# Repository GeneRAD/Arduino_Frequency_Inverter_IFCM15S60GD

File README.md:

# Frequency-Inverter-IFCM15S60GD
A frequency inverter with IFCM15S60GD up to 2kW.

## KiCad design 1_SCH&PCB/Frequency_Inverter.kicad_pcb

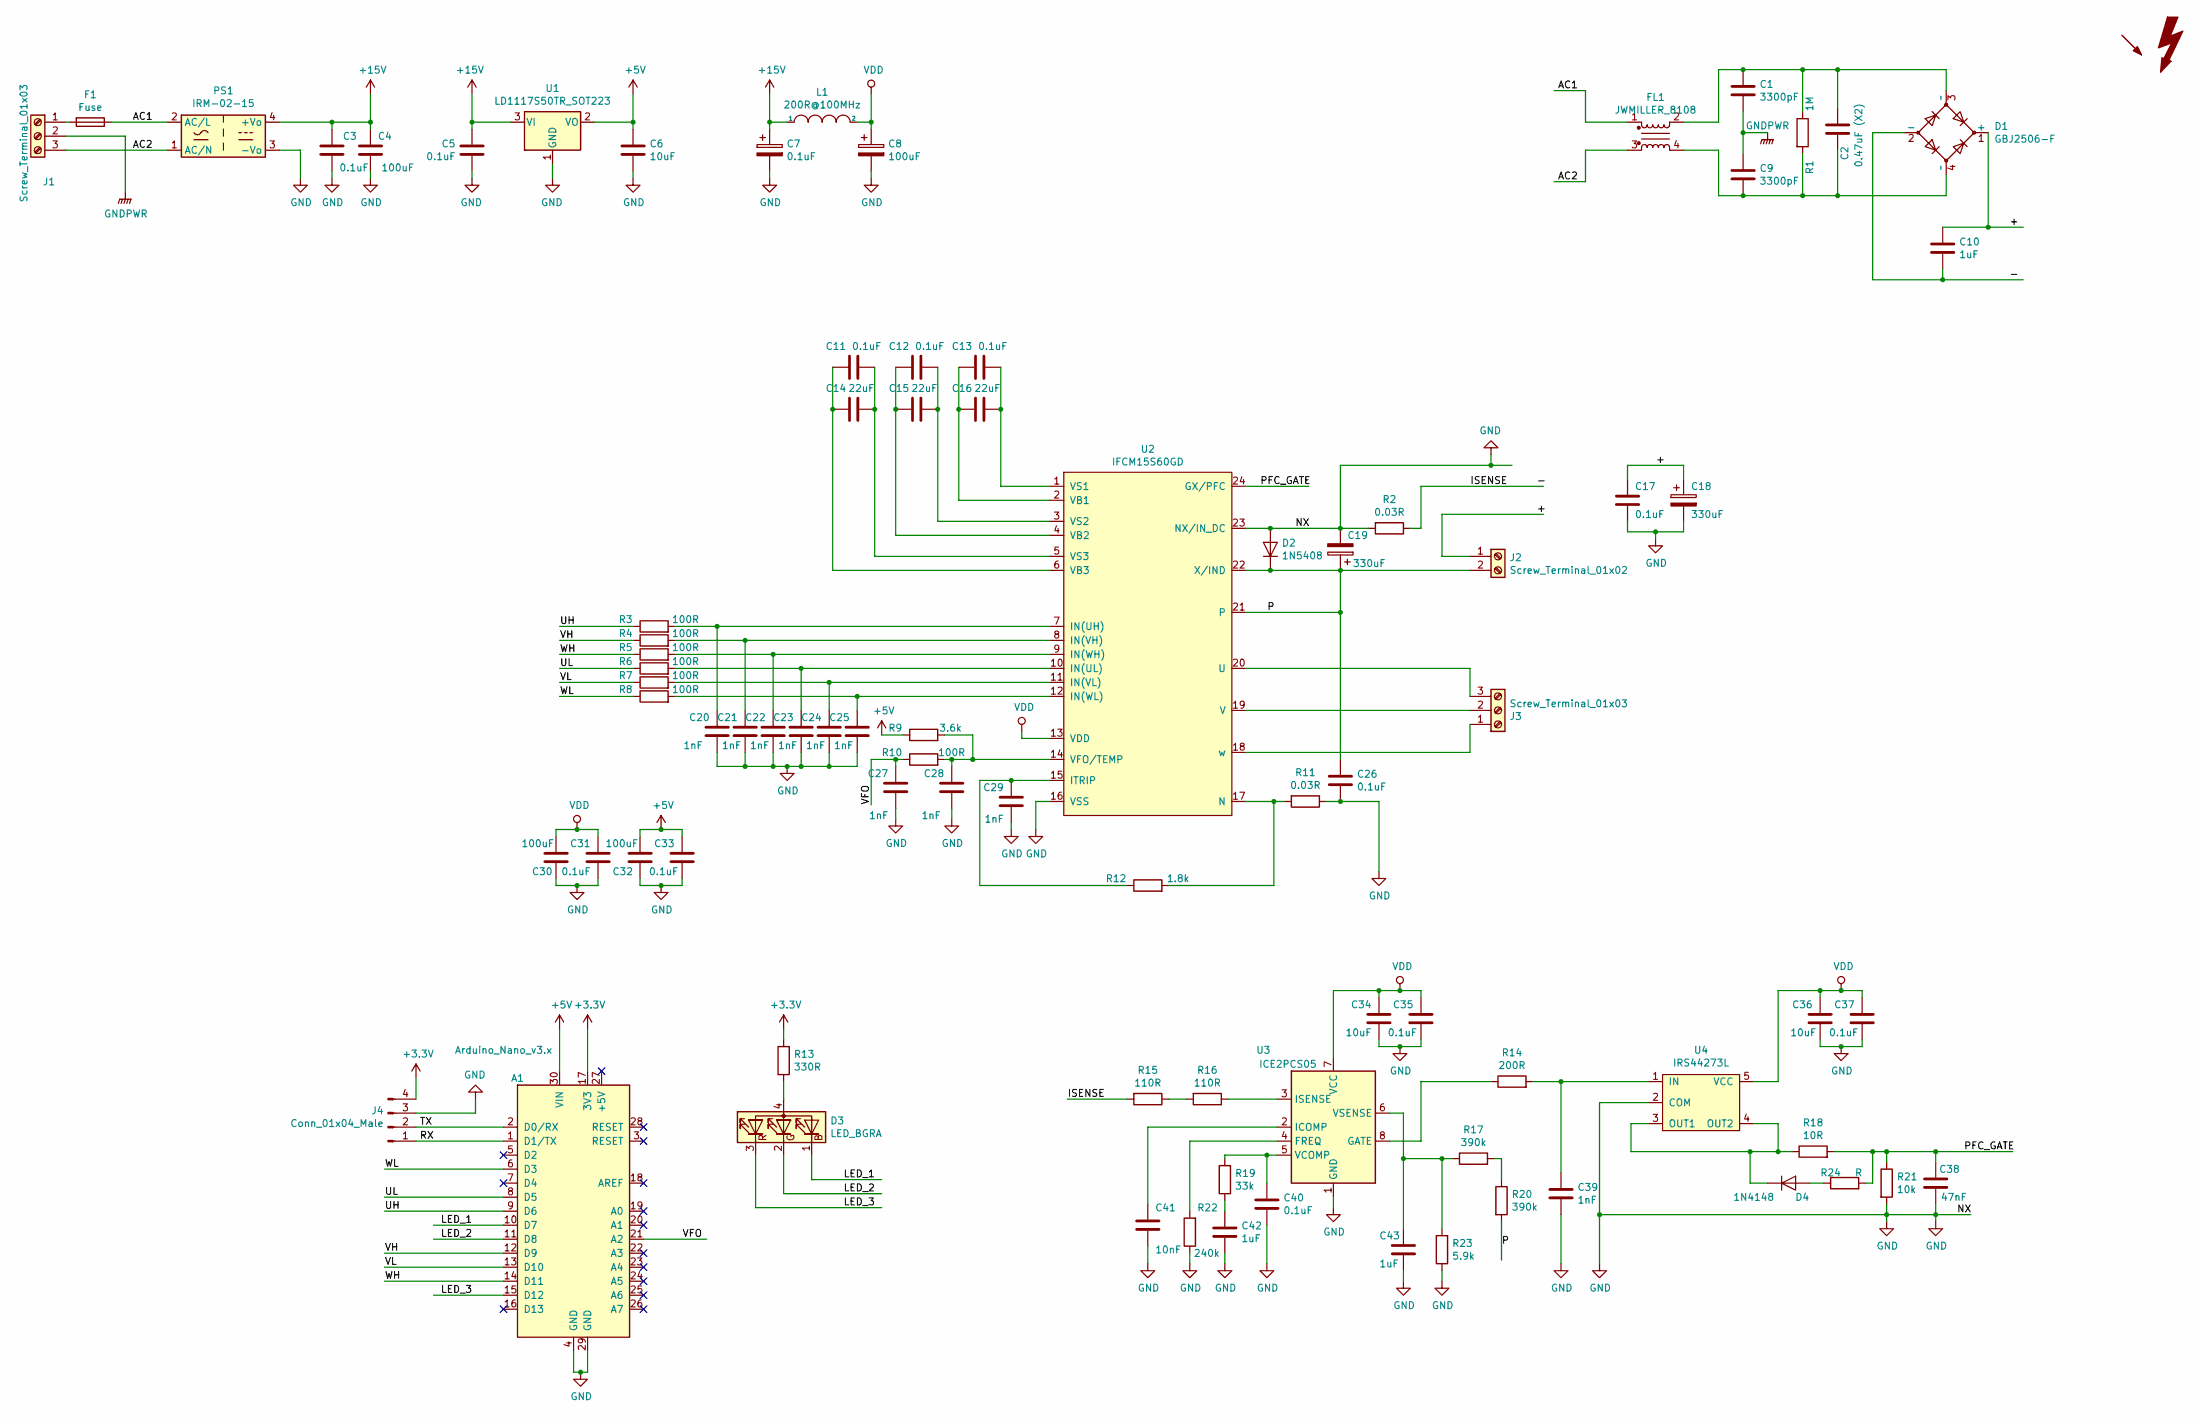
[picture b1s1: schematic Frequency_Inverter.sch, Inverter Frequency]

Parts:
A1: Arduino_Nano_v3.x; Arduino_Nano
C1, C9: 3300pF; C_Disc_D7.5mm_W5.0mm_P7.50mm
C2: 0.47uF (X2); C_Rect_L26.5mm_W7.0mm_P22.50mm_MKS4
C3, C5, C7, C11, C12, C13, C31, C33, C35, C37, C40: 0.1uF; C_0805_2012Metric_Pad1.15x1.40mm_HandSolder
C4, C8, C30, C32: 100uF; CP_Elec_6.3x4.5
C6, C34, C36: 10uF; C_0805_2012Metric_Pad1.15x1.40mm_HandSolder
C10: 1uF; C_1825_4564Metric_Pad1.88x6.70mm_HandSolder
C14, C15, C16: 22uF; C_1206_3216Metric_Pad1.42x1.75mm_HandSolder
C17, C26: 0.1uF; C_1825_4564Metric_Pad1.88x6.70mm_HandSolder
C18, C19: 330uF; CP_Radial_D35.0mm_P10.00mm_SnapIn
C20, C21, C22, C23, C24, C25, C27, C28, C29, C39: 1nF; C_0805_2012Metric_Pad1.15x1.40mm_HandSolder
C38: 47nF; C_0805_2012Metric_Pad1.15x1.40mm_HandSolder
C41: 10nF; C_0805_2012Metric_Pad1.15x1.40mm_HandSolder
C42, C43: 1uF; C_0805_2012Metric_Pad1.15x1.40mm_HandSolder
D1: GBJ2506-F; Diode_Bridge_Vishay_KBL
D2: 1N5408; D_DO-201AD_P15.24mm_Horizontal
D3: LED_BGRA; LED_Cree-PLCC4_5x5mm_CW
D4: 1N4148; D_0805_2012Metric
F1: Fuse; Fuse_Littelfuse-LVR100
FL1: JWMILLER_8108; L_CommonMode_Wuerth_WE-CMB-XS
J1, J3: Screw_Terminal_01x03; TerminalBlock_Altech_AK300-3_P5.00mm
J2: Screw_Terminal_01x02; TerminalBlock_Altech_AK300-2_P5.00mm
J4: Conn_01x04_Male; PinHeader_1x04_P2.54mm_Horizontal
L1: 200R@100MHz; L_0805_2012Metric_Pad1.15x1.40mm_HandSolder
PS1: IRM-02-15; Converter_ACDC_MeanWell_IRM-02-xx_THT
R1: 1M; R_2512_6332Metric_Pad1.52x3.35mm_HandSolder
R2, R11: 0.03R; R_1218_3246Metric_Pad1.22x4.75mm_HandSolder
R3, R4, R5, R6, R7, R8, R10: 100R; R_0805_2012Metric_Pad1.15x1.40mm_HandSolder
R9: 3.6k; R_0805_2012Metric_Pad1.15x1.40mm_HandSolder
R12: 1.8k; R_0805_2012Metric_Pad1.15x1.40mm_HandSolder
R13: 330R; R_0805_2012Metric_Pad1.15x1.40mm_HandSolder
R14: 200R; R_0805_2012Metric_Pad1.15x1.40mm_HandSolder
R15, R16: 110R; R_0805_2012Metric_Pad1.15x1.40mm_HandSolder
R17, R20: 390k; R_0805_2012Metric_Pad1.15x1.40mm_HandSolder
R18: 10R; R_0805_2012Metric_Pad1.15x1.40mm_HandSolder
R19: 33k; R_0805_2012Metric_Pad1.15x1.40mm_HandSolder
R21: 10k; R_0805_2012Metric_Pad1.15x1.40mm_HandSolder
R22: 240k; R_0805_2012Metric_Pad1.15x1.40mm_HandSolder
R23: 5.9k; R_0805_2012Metric_Pad1.15x1.40mm_HandSolder
R24: R; R_0805_2012Metric_Pad1.15x1.40mm_HandSolder
U1: LD1117S50TR_SOT223; SOT-223-3_TabPin2
U2: IFCM15S60GD; IFCM15S60_24_pins
U3: ICE2PCS05; SOIC-8_3.9x4.9mm_P1.27mm
U4: IRS44273L; SOT-23-5_HandSoldering

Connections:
+3V3: A1.17 (3V3), J4.4, R13.2
+5V: A1.30 (VIN), C6.1, C32.1, C33.2, R9.1, U1.2 (VO)
+15V: C3.1, C4.1, C5.1, C7.1, L1.1, PS1.4 (+Vo), U1.3 (VI)
/+: C10.1, C17.1, C18.1, D1.1 (+), J2.1
/-: C10.2, D1.2 (-), R2.1, R15.2
/AC1: F1.1, FL1.1, PS1.2 (AC/L)
/AC2: FL1.3, J1.3, PS1.1 (AC/N)
/LED_1: A1.10 (D7), D3.1 (BK)
/LED_2: A1.11 (D8), D3.2 (GK)
/LED_3: A1.15 (D12), D3.3 (RK)
/P: C19.1, C26.1, D2.1 (K), J2.2, R20.2, U2.21, U2.22 (X/IND)
/PFC_GATE: C38.2, R18.2, R21.1, R24.2, U2.24 (GX/PFC)
/RX: A1.1 (D1/TX), J4.1
/TX: A1.2 (D0/RX), J4.2
/UH: A1.9 (D6), R3.1
/UL: A1.8 (D5), R6.1
/VFO: A1.21 (A2), C27.2, R10.1
/VH: A1.12 (D9), R4.1
/VL: A1.13 (D10), R7.1
/WH: A1.14 (D11), R5.1
/WL: A1.6 (D3), R8.1
GND: A1.4 (GND), A1.29 (GND), C3.2, C4.2, C5.2, C6.2, C7.2, C8.2, C17.2, C18.2, C19.2, C20.1, C21.1, C22.1, C23.1, C24.1, C25.1, C26.2, C27.1, C28.1, C29.1, C30.2, C31.1, C32.2, C33.1, C34.1, C35.1, C36.1, C37.1, C38.1, C39.2, C40.2, C41.2, C42.2, C43.2, D2.2 (A), J4.3, PS1.3 (-Vo), R2.2, R11.1, R21.2, R22.1, R23.1, U1.1 (GND), U2.16 (VSS), U2.23 (NX/IN_DC), U3.1 (GND), U4.2 (COM)
GNDPWR: C1.2, C9.1, J1.2
unnamed: C1.1, C2.1, D1.3 (~~), FL1.2, R1.1
unnamed: C2.2, C9.2, D1.4 (~~), FL1.4, R1.2
unnamed: C11.1, C14.1, U2.6 (VB3)
unnamed: C11.2, C14.2, U2.5 (VS3)
unnamed: C12.1, C15.1, U2.4 (VB2)
unnamed: C12.2, C15.2, U2.3 (VS2)
unnamed: C13.1, C16.1, U2.2 (VB1)
unnamed: C13.2, C16.2, U2.1 (VS1)
unnamed: C20.2, R3.2, U2.7 (IN(UH))
unnamed: C21.2, R4.2, U2.8 (IN(VH))
unnamed: C22.2, R5.2, U2.9 (IN(WH))
unnamed: C23.2, R6.2, U2.10 (IN(UL))
unnamed: C24.2, R7.2, U2.11 (IN(VL))
unnamed: C25.2, R8.2, U2.12 (IN(WL))
unnamed: C28.2, R9.2, R10.2, U2.14 (VFO/TEMP)
unnamed: C29.2, R12.1, U2.15 (ITRIP)
unnamed: C39.1, R14.2, U4.1 (IN)
unnamed: C40.1, R19.2, U3.5 (VCOMP)
unnamed: C41.1, U3.2 (ICOMP)
unnamed: C42.1, R19.1
unnamed: C43.1, R17.1, R23.2, U3.6 (VSENSE)
unnamed: D3.4 (A), R13.1
unnamed: D4.1 (K), R18.1, U4.3 (OUT1), U4.4 (OUT2)
unnamed: D4.2 (A), R24.1
unnamed: F1.2, J1.1
unnamed: J3.1, U2.18 (w)
unnamed: J3.2, U2.19 (V)
unnamed: J3.3, U2.20 (U)
unnamed: R11.2, R12.2, U2.17 (N)
unnamed: R14.1, U3.8 (GATE)
unnamed: R15.1, R16.2
unnamed: R16.1, U3.3 (ISENSE)
unnamed: R17.2, R20.1
unnamed: R22.2, U3.4 (FREQ)
VDD: C8.1, C30.1, C31.2, C34.2, C35.2, C36.2, C37.2, L1.2, U2.13 (VDD), U3.7 (VCC), U4.5 (VCC)

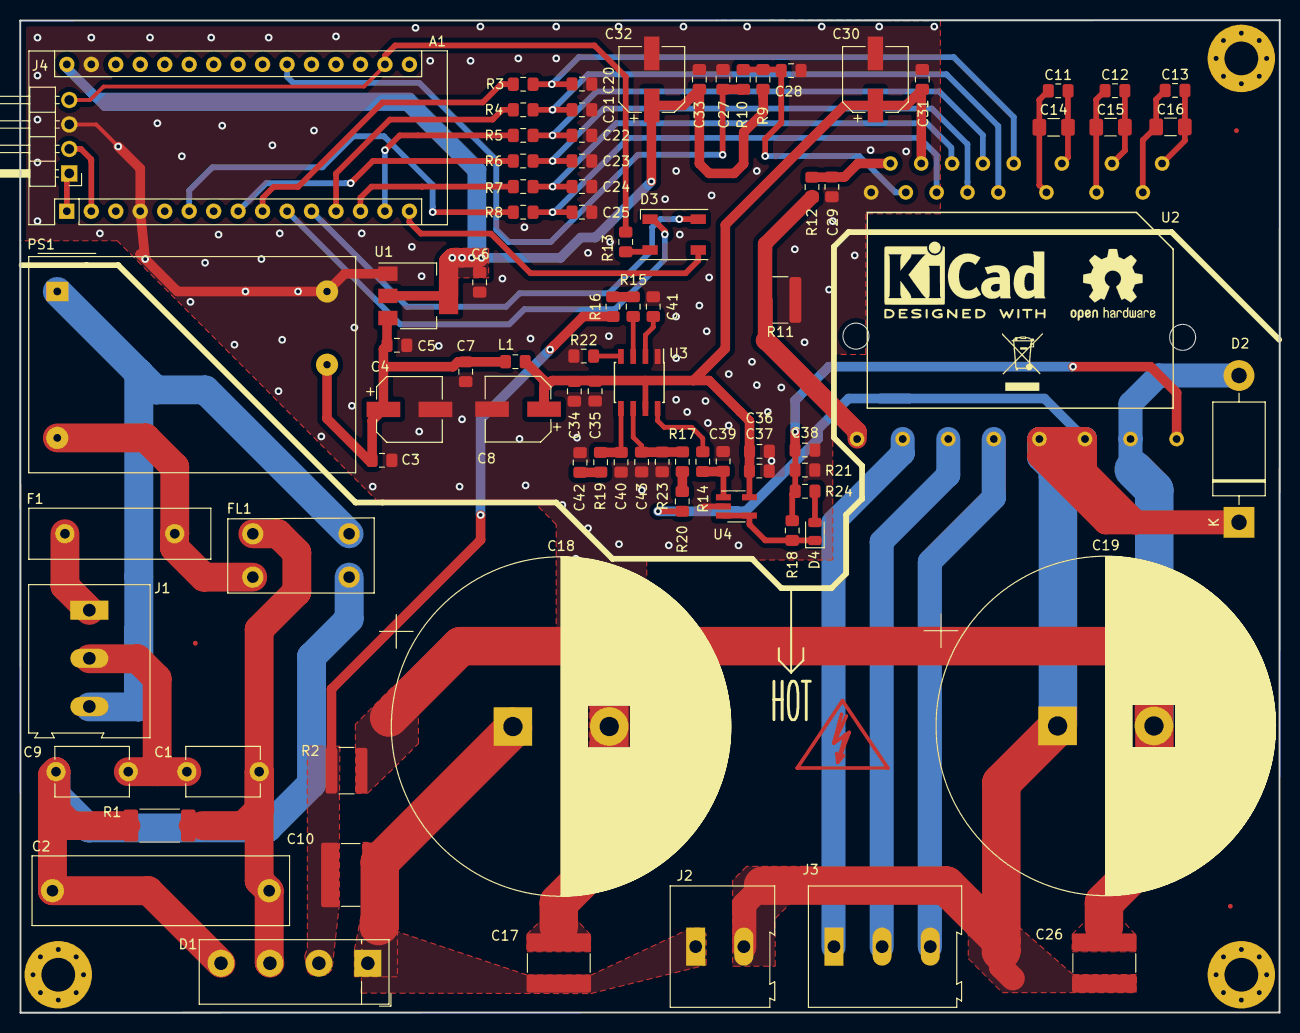
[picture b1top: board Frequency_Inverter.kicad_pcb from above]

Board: 2 copper layers, 130.7 x 103.0 mm, 84 parts (0 on the bottom side), 58 nets.
